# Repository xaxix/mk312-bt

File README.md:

# MK-312BT V1.3

Documentation at : http://tinyurl.com/mk312bt-info

Forum (for questions/discussion): https://metafetish.club ([Estim
Specific Category Here](https://metafetish.club/c/estim), but may not
include all estim messages)

## Board ordering instructions

Preferred board house is https://jlcpcb.com

You'll need 2 gerber zip files from the gerbers directory (click links below to download):

- [MK-312 V1.2 Front Panel](https://github.com/buttshock/mk312-bt/blob/master/gerbers/ZIP%20FILES/MK-312BT%20Front%20Panel%20V1.2%20Gerber.zip?raw=true)
- [MK-312 V1.3 Main Board](https://github.com/buttshock/mk312-bt/blob/master/gerbers/ZIP%20FILES/MK-312BT%20Main%20Boards%20V1.3%20Gerber.zip?raw=true)

**NOTE:** Order Front Panel and Main Board as seperate items (but they
can be in the same cart), due to difference in "Different Design"
setting. See below.

- Base Material: Standard "FR4"
- Layers: "2" Layer (should be detected when you upload the zip with the gerbers)
- Dimensions: (should be detected when you upload the zip with the gerbers)
- Quantity: No requirement, choose whatever you like
- Product Type: "Industrial/Consumer electronics"
- Different Design 
   - Main Boards: "2"
   - Front Panel: "1"
- Delivery Format: "Single PCB"
- Thickness: "1.6"
- PCB Color:
   - Main Boards: No requirement, choose whatever you like
   - Front Panel: Black is recommended, but not required. Choose whatever you like otherwise.
- Silkscreen: "White"
- Surface finish: "LeadFree HASL" or "HASL(with lead)
- Copper weight: 1oz
- Via Covering: Tented (?)
- Board Outline Tolerance: "+-0,2mm(Regular)"
- Confirm Production file: "No"
- Remove Order Number: "No"
- Flying Probe Test: "Fully Test"
- Gold fingers: "No"
- Castellated Holes: "No"
- Edge Plating: "No"
- PCB Remark:
   - Main Boards: V Score the Main Boards panel as indicated.
   - Front Panel: Place all Fab Markings (Serial Numbers/Date Codes) on the BOTTOM side of the front panel board.
   
## Board Assembly Instructions - IMPORTANT

1. Trim Potentiometer knobs to correct length if desired
2. Use black permanent marker to black out front panel hole walls if
   desired
3. Cut the tabs off of the base of the pots so the board sits flush
   with the display facade if desired
4. To correctly fit LCD - solder header to LCD board first. Next
   insert LCD panel into front panel daughter board. Then put screws
   on front panel facade and finger tighten M2.5 screws first. Adjust
   positions as needed so everything lines up and sits well. Finally
   solder LCD header to front panel daughter board.
5. Make sure Pin 32 (LED2) on the HC-05 module is actually soldered
   and making connection to the ZS-040 break out board or "Radio" LED
   may not function on the front panel
6. Be very careful not to bridge pins when soldering the LM 2941
   (U14). Apply heat to 1 pad only and carefully apply solder. If a
   bridge occurs - remove the IC, clean the pads throughly with flux
   and solder wick and then retry. Pins 2 and 3 can be bridged because
   they are both ground. Ensure that no other pins are bridged. Check
   with multimeter continuity tester for bridges before power on!
7. Make sure to check the orientation of all electrolytic caps. (+)
   indicates the positive and a solid white "|" indicates the negative.
8. **MAKE SURE YOUR POWER PLUG IS CENTER POSITIVE OR THINGS WILL GO
   BADLY.** If you fuck up and plug in a reversed polarity supply -
   replace electrolytic caps C1 and C4.
9. Please remember to adjust the LCD contrast potentiometer - if
   incorrectly set the unit and backlight will power on but the
   interface will not be displayed.
10. Place transformers with P facing the output jacks (yes we are
    using the transformers "backwards" if you follow orientation given
    in the transformer datasheet )
11. Trim pins of 4066 IC (U3) Socket on the front panel board flush
    before soldering so buttons can clear. If the buttons still
    interfere, carefully disassemble the button and cut off the bit of
    the plastic housing that interferes with the 4066 IC socket pins.
12. Using side cutters cut off the screw boss/screw mount on the case
    that touches/interferes with the ribbon cable socket on the
    display board.
13. The LCD display has metal retention tabs that may short the
    soldered leads of C43. When installing the display board ensure
    that this does not happen (shorten the capacitor leads and bend
    the offending metal tab out of the way if necessary
14. If Error 20 is encountered on first boot:
   - Check that all FETs and Transformers are turned in the correct direction
   - Check that resistors R35 and R46 are the correct 200k values
   - [See this thread on the message board](https://metafetish.club/t/mk-312bt-failure-20/)

## MK312-BT Firmware

1. We are using an external 8mhz crystal instead of the internal RC
   oscillator that the original uses. We need to set the fuses to
   enable this. 
   - LOW FUSE: 0xFF 
   - HIGH FUSE: 0xDC
2. A patched version of buttshock-et312-frankenbutt-f005 is
   recommended.
3. The firmware needs to be changed to replace the up/down arrows on
   the UI with left right arrows (this is because the LCD we use has a
   different character set)
4. Obtain or modify a copy of the firmware and flash the result onto
   the AVR.
5. If you don't want to use an external crystal - we need to set the
   calibration byte for the internal oscillator. If programming a
   blank chip you first need to read the calibration bytes of that
   part (i.e. using avrdude -t “dump calibration” the fourth byte is
   the calibration byte for 8MHz or use atmel studio to read the
   oscillator calibration byte). Then program that byte into 0x3fff in
   your firmware. These bytes will differ on different chips even from
   the same batch. The firmware reads that byte to set OSCCAL on
   startup. If the byte is inaccurate various problems and failures
   will occur related to timing, interrupts, and serial communication.
   Just use an external crystal dammit.

## MK312-BT Original Fab Notes

(These are the old fab notes from the repo, mostly kept here for
history sake. Ordering instructions above cover most of this.)

### Main Boards

1. V Score the Main Boards panel as indicated.
2. Main Boards has 2 board designs panelized on 1 panel.
3. Thickness is standard 1.6mm (0.063inches)
4. Board is 2 layers
5. HASL Finish - Pb Free Preferred if possible, otherwise Pb HASL is OK
6. 1oz copper
7. FR4 material
8. Main Boards : Green solder mask, White Silkscreen (silkscreen BOTH top and bottom sides)
9. ITAR : NO
10. IPC-A-610 - Class2 (If possible - otherwise ignore)
11. Main Board Dimensions : (193.04mm x 104.14mm) or (7.600 inches x 4.100 inches) 

### Front Panel Boards

1. Place all Fab Markings (Serial Numbers/Date Codes) on the BOTTOM side of the front panel board. 
2. Thickness is standard 1.6mm (0.063inches)
3. Board is 2 layers
4. HASL Finish - Pb Free Preferred if possible, otherwise Pb HASL is OK
5. 1oz copper
6. FR4 material
7. Front Panel Boards : Black Solder Mask, While Silkscreen
8. ITAR : NO
9. IPC-A-610 - Class2 (If possible - otherwise ignore)
10. Front Panel Board Dimensions :  (196.85mm x 58.72mm) or (7.750inches x 2.312inches) 

## Bluetooth Serial Configuration

Refer to
[https://www.itead.cc/wiki/Serial_Port_Bluetooth_Module_(Master/Slave)_:_HC-05](https://www.itead.cc/wiki/Serial_Port_Bluetooth_Module_(Master/Slave)_:_HC-05)
for more information.

```
// Test command to check if we are communicating (expect to receive OK)
AT

//Name the module
AT+NAME=MK-312BT 

//Set baud rate to be same as the ATMEGA16
AT+UART=19200,0,0

//Set the pairing password
AT+PSWD=1234

//Set the LED Indicator polarity (1 = High Drive 0 = Low Drive)
AT+POLAR=1,1

// Reduce power consumption by increasing the scan interval. Without
// this it consumes ~43mA when not connected and causes the 5v regulator
// to get toasty (but still within operational temp range)
AT+IPSCAN=1024,1,1024,1 
```

To do this automatically:
1. Solder Pin32 of the HC05 module (See [bluetooth/HC05PINOUT.PNG](https://github.com/buttshock/mk312-bt/blob/master/bluetooth_conf/HC05PINOUT.png) for reference)
2. Flash the included bin file onto the ATMEGA16
3. Plug the HC-05 bluetooth radio into the board (ensure pin 32 is
   soldered to the carrier board)
4. Place HC-05 in command mode by holding down the button on the HC-05
   module, power up MK-312BT and release button after 2 seconds. LEDs
   on HC-05 will blink slowly (0.5 Hz) to indicate command mode.
5. Watch GUI until it says the HC-05 configuration is finished and
   flash normal firmware back on to the ATMEGA16
6. If program stops on "Communicating with HC-05" make sure OSCCAL
   value for 8 MHz R/C position is copied to &H3FFF of bin location or
   use external 8 MHz crystal with appropriate fuse bits set (FFS use
   the external crystal)

## 3D Printable Case

STL files for a 3D printable case for the MK312 are available in the
case/ directory. For hardware, this case requires:

- 4 M2.5x20 screws
- up to 3 M2.5x5 screws
- some dampening for the battery (double sided foam tape may work)

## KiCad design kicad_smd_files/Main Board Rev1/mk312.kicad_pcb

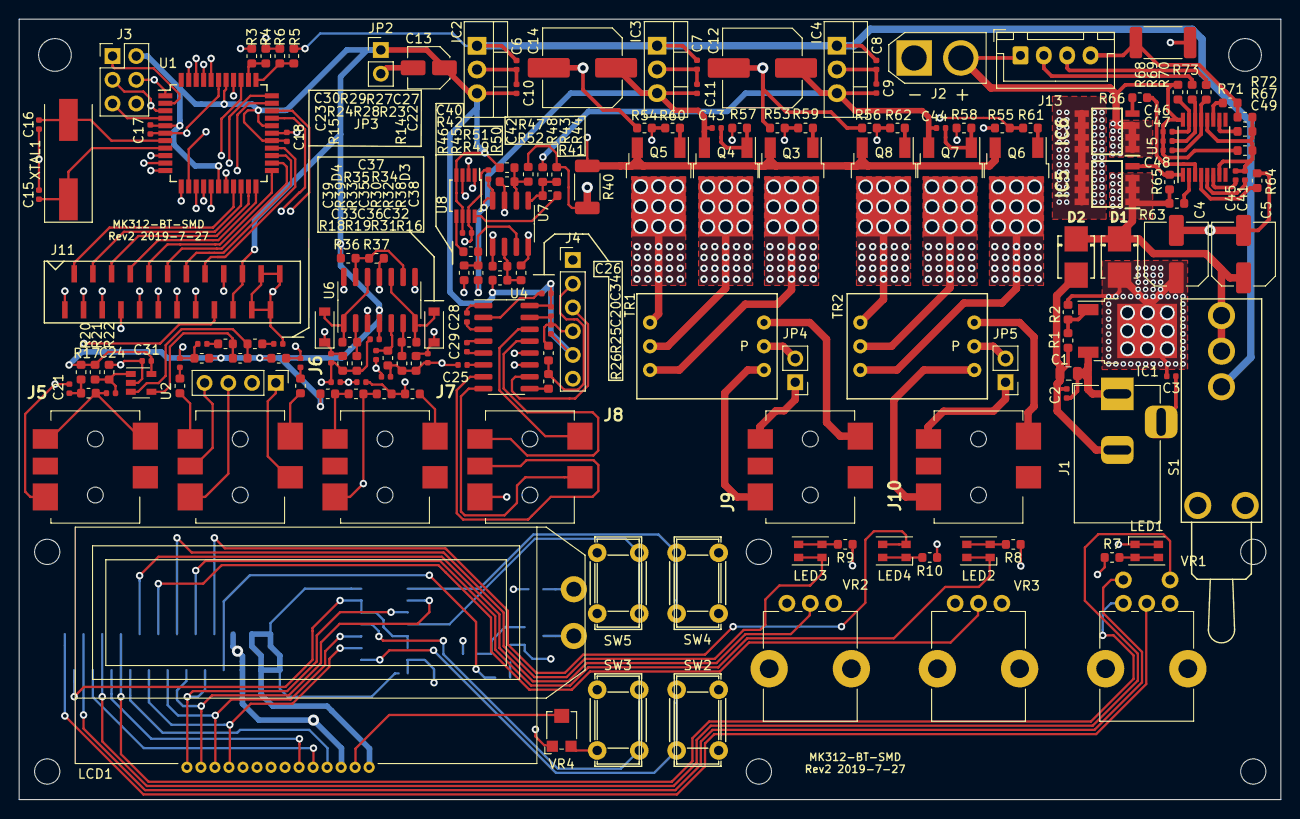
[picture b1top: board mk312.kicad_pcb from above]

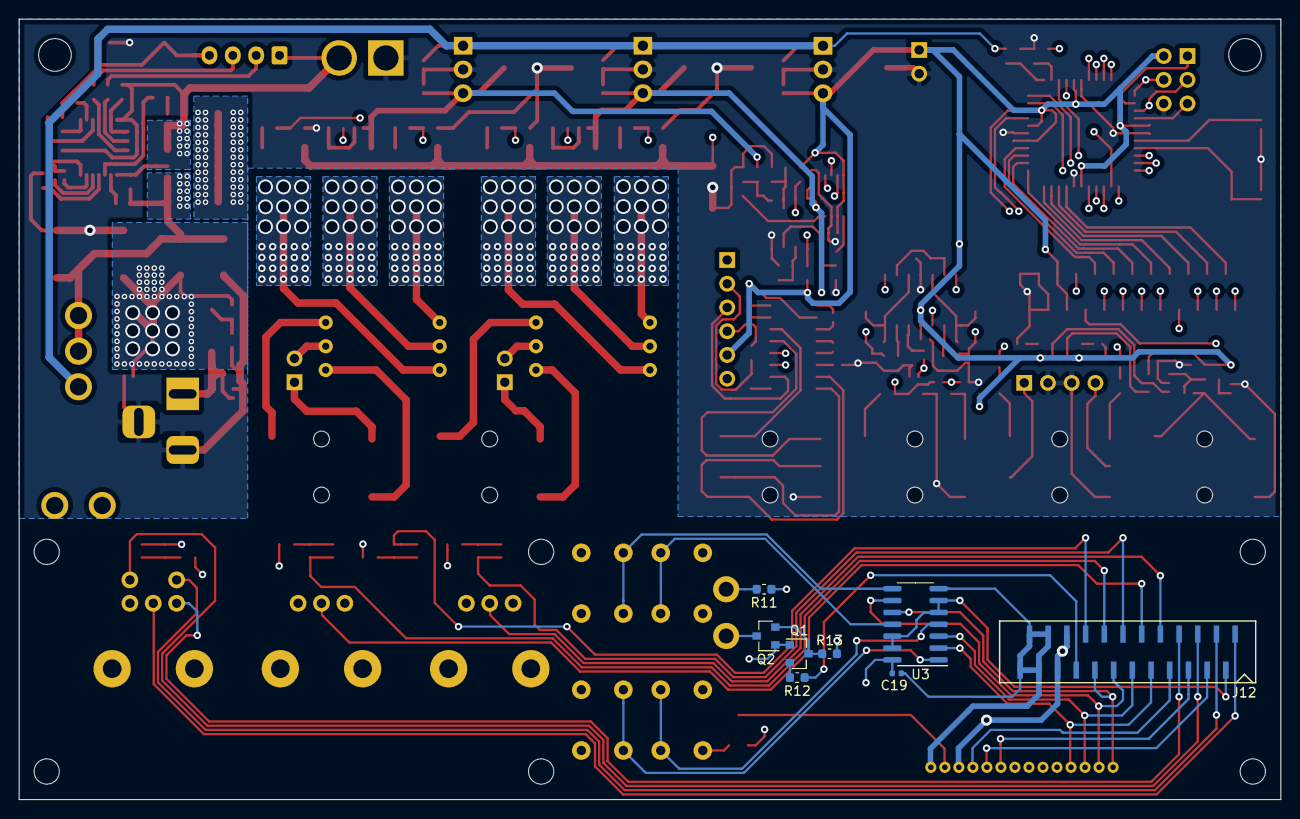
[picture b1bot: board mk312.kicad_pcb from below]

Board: 4 copper layers, 135.0 x 83.5 mm, 190 parts (8 on the bottom side), 161 nets.

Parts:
C1: 10uF; C_0805_2012Metric
C2, C3, C6, C7, C8, C9, C10, C11, C17, C18, C19, C20, C24, C31, C34, C35, C36, C37, C40, C41, C42, C43, C44, C45, C46, C47, C48: 0.1uF; C_0402_1005Metric
C4, C5: 100uF; C_Elec_6.3x7.7
C12, C14: 470uF; C_Elec_8x10.2
C13: 10uF; C_Elec_4x5.8
C15, C16: 18pF; C_0402_1005Metric
C21, C22, C23, C25, C26, C27, C28, C29, C30, C38, C39: 1uF; C_0402_1005Metric
C32, C33: 1nF; C_0402_1005Metric
C49: 2.2uF; C_0603_1608Metric
D1, D2: GF1G-E3/67A; DO-214BA
D3, D4: 1N4148W-E3-08; D_SOD-123
H1, H2, H3, H4, H5, H6: MountingHole; MountingHole_2.7mm_M2.5
H7, H8: MountingHole; MountingHole_3.5mm
IC1: LMS8117ADTX-ADJ; TO-252-2
IC2: L7805CV; TO-220-3_Vertical
IC3, IC4: L7809ABV; TO-220-3_Vertical
IC5, IC6: SI4435FDY-T1-GE3; SOIC127P600X175-8N
J1: Barrel_Jack_MountingPin; BarrelJack_Horizontal
J2: +12V Battery; AMASS_XT30U-M_1x02_P5.0mm_Vertical
J3: Conn_02x03_Odd_Even; PinHeader_2x03_P2.54mm_Vertical
J4: RADIO INTERFACE; PinHeader_1x06_P2.54mm_Vertical
J5: MIC INPUT; SJ13515SMTTR
J6: LINE INPUT; SJ13515SMTTR
J7: REMOTE INPUT; SJ13515SMTTR
J8: LINK INPUT; SJ13515SMTTR
J9: OUTPUT A; SJ13515SMTTR
J10: OUTPUT B; SJ13515SMTTR
J11, J12: Conn_01x24_Male; HFW24S-2STE1LF
J13: Conn_01x04; JST_XH_B4B-XH-A_1x04_P2.50mm_Vertical
JP2: +5V; PinHeader_1x02_P2.54mm_Vertical
JP3: AUX LINE IN; PinHeader_1x04_P2.54mm_Vertical
JP4: A RING; PinHeader_1x02_P2.54mm_Vertical
JP5: B RING; PinHeader_1x02_P2.54mm_Vertical
LCD1: NHD-C0216AZ-FSW-GBW
LED1: POWER; LED_Cree-PLCC4_3.2x2.8mm_CCW
LED2: OUTPUT B; LED_Cree-PLCC4_3.2x2.8mm_CCW
LED3: OUTPUT A; LED_Cree-PLCC4_3.2x2.8mm_CCW
LED4: STATE; LED_Cree-PLCC4_3.2x2.8mm_CCW
Q1, Q2: MMBT3904-7-F; SOT-23
Q3, Q5, Q6, Q8: IRFR9024NTRPBF; TO-252-2
Q4, Q7: IRLR120NTRPBF; TO-252-2
R1, R14, R15, R16, R19, R64, R67, R68, R69, R70, R71: 1K; R_0603_1608Metric
R2: 110; R_0603_1608Metric
R3, R21, R22, R30, R31, R37, R38, R39, R41, R42, R43, R44, R45, R46, R47, R49, R51, R52, R53, R54, R55, R56: 100K; R_0603_1608Metric
R4, R23, R24, R27, R32, R33: 20K; R_0603_1608Metric
R5, R25, R57, R58, R59, R60, R61, R62: 10K; R_0603_1608Metric
R6: 3.3K; R_0603_1608Metric
R7, R8, R9, R10: 390; R_0603_1608Metric
R11: 130; R_0603_1608Metric
R12, R13, R18: 1.5K; R_0603_1608Metric
R17, R20: 2.2K; R_0603_1608Metric
R26, R29: 4.7K; R_0603_1608Metric
R28, R34, R35, R36, R65: 1M; R_0603_1608Metric
R40: 0.5R 1/2W; R_2010_5025Metric
R48, R50: 200K; R_0603_1608Metric
R63, R66: 5.1K; R_0603_1608Metric
R72: 51; R_0603_1608Metric
R73: 0.2R 2W; R_2512_6332Metric
S1: POWER; E-Switch_M7_SPDT
SW2: LEFT/DOWN; E-Switch_Tactile_TL1105
SW3: OK; E-Switch_Tactile_TL1105
SW4: RIGHT/UP; E-Switch_Tactile_TL1105
SW5: MENU; E-Switch_Tactile_TL1105
TR1, TR2: 42TL004; 42TL
U1: ATmega16-16AU; TQFP-44_10x10mm_P0.8mm
U2: MCP6L01U; SOT-23-5
U3: CD4066B; SOIC-14_3.9x8.7mm_P1.27mm
U4: SP232E; SOIC-16_3.9x9.9mm_P1.27mm
U5: S-8254A; TSSOP-16_4.4x5mm_P0.65mm
U6: LM324N; SOIC-14_3.9x8.7mm_P1.27mm
U7: LM358N; SOIC-8_3.9x4.9mm_P1.27mm
U8: LTC1661; MSOP-8_3x3mm_P0.65mm
VR1: MULTI-ADJ; Potentiometer_Alps_RK09K_Dual_Vertical
VR2: LEVEL A; Potentiometer_Alps_RK09K_Single_Vertical
VR3: LEVEL B; Potentiometer_Alps_RK09K_Single_Vertical
VR4: LCD CONTRAST; Potentiometer_Bourns_TC33X_Vertical
XTAL1: 8.0 MHz; Crystal_SMD_HC49-SD

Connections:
+5V: C10.1, C13.1, C17.1, C18.1, C20.1, C26.1, C31.2, C34.2, C37.2, C40.1, IC2.3, J3.2, J4.5, J11.19, J11.20, JP2.1, R18.2, R20.1, R21.1, R23.1, R24.2, R36.2, R47.1, R49.1, U1.5, U1.17, U1.27, U1.29, U1.38, U2.5, U4.16, U6.4, U8.4, U8.6
+5VD: C19.1, J12.19, J12.20, LCD1.3, R7.1, R8.1, R9.1, R11.1, R13.2, U3.14, VR2.3, VR3.3, VR4.1
+9V1: C11.1, C14.1, C42.1, C43.2, IC3.3, Q4.3, R45.1, U7.8
+9V2: C9.1, C12.1, C44.2, IC4.3, Q7.3, R43.1
+12V: C6.1, C7.1, C8.1, IC2.1, IC3.1, IC4.1, R5.2, S1.1
+VDC: C1.1, C2.1, IC1.3, J1.1, R3.1
GND: C1.2, C2.2, C3.2, C4.2, C5.2, C6.2, C7.2, C8.2, C9.2, C10.2, C11.2, C12.2, C13.2, C14.2, C15.2, C16.2, C17.2, C18.2, C20.2, C21.2, C25.1, C27.2, C31.1, C32.2, C33.2, C34.1, C37.1, C38.2, C39.2, C40.2, C42.2, D2.2, IC2.2, IC3.2, IC4.2, J1.2, J1.3, J2.1, J3.6, J4.4, J5.S, J6.S, J7.S, J8.S, J11.21, J11.22, J11.23, J11.24, JP2.2, JP3.2, JP3.3, R1.2, R4.2, R6.2, R19.1, R22.1, R25.2, R30.2, R31.2, R32.2, R33.2, R37.1, R38.1, R39.1, R40.2, R44.2, R46.2, R48.2, R50.2, R53.2, R54.2, R55.2, R56.2, R64.1, R73.2, U1.6, U1.18, U1.28, U1.39, U2.2, U4.15, U6.11, U7.4, U8.7
GNDD: C19.2, J12.21, J12.22, J12.23, J12.24, LCD1.1, LED1.1, Q1.1, Q2.1, R10.1, SW2.2, SW3.2, SW4.2, SW5.2, U3.7, VR1.1, VR2.1, VR3.1, VR4.3
unnamed: C3.1, C4.1, D1.2, IC1.2, R2.2
unnamed: C5.1, D1.1, D2.1, IC5.1, IC5.2, IC5.3, R63.1, R65.1, S1.2, S1.3
unnamed: C15.1, U1.8, XTAL1.1
unnamed: C16.1, U1.7, XTAL1.2
unnamed: C21.1, R17.1, R20.2
unnamed: C22.1, R14.1
unnamed: C23.1, R15.1
unnamed: C24.1, J5.R, J5.T, R17.2
unnamed: C24.2, R21.2, R22.2, U2.1
unnamed: C25.2, U4.6
unnamed: C26.2, U4.2
unnamed: C27.1, R27.2
unnamed: C28.1, U4.1
unnamed: C28.2, U4.3
unnamed: C29.1, U4.4
unnamed: C29.2, U4.5
unnamed: C30.2, R29.2
unnamed: C35.2, R30.1, U6.5
unnamed: C36.2, R16.1, R31.1, U6.3
unnamed: C41.1, U5.5
unnamed: C41.2, C45.2, C49.2, R67.1, R72.2, U5.7, U5.12
unnamed: C43.1, Q4.1, R57.1
unnamed: C44.1, Q7.1, R58.1
unnamed: C45.1, U5.6
unnamed: C46.1, C47.1, C48.1, C49.1, IC6.1, IC6.2, IC6.3, J2.2, J13.1, R68.1, U5.16
unnamed: C46.2, R68.2, U5.15
unnamed: C47.2, R69.2, U5.14
unnamed: C48.2, R70.2, U5.13
unnamed: D3.2, R34.1, U6.7, U6.10
unnamed: D4.2, R35.1, U6.1, U6.12
unnamed: IC1.1, R1.1, R2.1
unnamed: IC5.4, R65.2, U5.1
unnamed: IC5.5, IC5.6, IC5.7, IC5.8, IC6.5, IC6.6, IC6.7, IC6.8
unnamed: IC6.4, R66.1
unnamed: J4.2, R25.1, R26.2
unnamed: J4.3, U4.10
unnamed: J6.R, R15.2
unnamed: J6.RN, JP3.4
unnamed: J6.T, R14.2
unnamed: J6.TN, JP3.1
unnamed: J7.R, R18.1, R19.2
unnamed: J7.T, R16.2
unnamed: J8.R, U4.13
unnamed: J8.RN, U4.7
unnamed: J8.T, U4.14
unnamed: J8.TN, U4.8
unnamed: J9.R, JP4.1
unnamed: J9.S, TR1.1
unnamed: J9.T, TR1.3
unnamed: J10.R, JP5.1
unnamed: J10.S, TR2.1
unnamed: J10.T, TR2.3
unnamed: J13.2, R69.1
unnamed: J13.3, R70.1
unnamed: J13.4, R71.1, R72.1, R73.1
unnamed: JP4.2, TR1.2
unnamed: JP5.2, TR2.2
unnamed: LCD1.2, VR4.2
unnamed: LCD1.A, R11.2
unnamed: LCD1.K, Q2.3
unnamed: LED1.2, R7.2
unnamed: LED2.2, R8.2
unnamed: LED3.2, R9.2
unnamed: LED4.1, R10.2
unnamed: Q1.2, R12.2
unnamed: Q1.3, Q2.2, R13.1
unnamed: Q3.1, R59.1
unnamed: Q3.2, TR1.6
unnamed: Q4.2, TR1.5
unnamed: Q5.1, R60.1
unnamed: Q5.2, TR1.4
unnamed: Q6.1, R61.1
unnamed: Q6.2, TR2.6
unnamed: Q7.2, TR2.5
unnamed: Q8.1, R62.1
unnamed: Q8.2, TR2.4
unnamed: R3.2, R4.1, U1.35
unnamed: R5.1, R6.1, U1.34
unnamed: R26.1, U4.9
unnamed: R27.1, R28.2, U2.3
unnamed: R28.1, R29.1, U2.4
unnamed: R32.1, R34.2, U6.6
unnamed: R33.1, R35.2, U6.2
unnamed: R36.1, R37.2, U6.9, U6.13
unnamed: R41.1, R43.2, R44.1, U7.5
unnamed: R41.2, U8.8
unnamed: R42.1, R45.2, R46.1, U7.3
unnamed: R42.2, U8.5
unnamed: R47.2, R48.1, R52.2, U7.6
unnamed: R49.2, R50.1, R51.2, U7.2
unnamed: R51.1, R57.2, U7.1
unnamed: R52.1, R58.2, U7.7
unnamed: R63.2, U5.2
unnamed: R64.2, U5.4
unnamed: R66.2, U5.3
unnamed: R67.2, U5.10
unnamed: R71.2, U5.11
unnamed: SW2.1, U3.1
unnamed: SW3.1, U3.4
unnamed: SW4.1, U3.8
unnamed: SW5.1, U3.11
PA0: Q3.3, Q5.3, Q6.3, Q8.3, R40.1, U1.37
PA1: C32.1, C35.1, J11.5, U1.36
PA1-PANEL: J12.5, VR1.2
PA4: J11.9, U1.33
PA4-PANEL: J12.9, VR2.2
PA5: J11.11, U1.32
PA5-PANEL: J12.11, VR3.2
PA6: C39.1, D4.1, R39.2, U1.31
PA7: C38.1, D3.1, R38.2, U1.30
PB0: R55.1, R61.2, U1.40
PB1: R56.1, R62.2, U1.41
PB2: R53.1, R59.2, U1.42
PB3: R54.1, R60.2, U1.43
PB5: J3.4, U1.1, U8.3
PB6: J3.1, U1.2
PB7: J3.3, U1.3, U8.2
PC0: J11.2, U1.19
PC0-PANEL: J12.2, U3.5, U3.6, U3.12, U3.13
PC1: J11.4, U1.20
PC1-PANEL: J12.4, LCD1.5
PC2: J11.6, U1.21
PC2-PANEL: J12.6, LCD1.6
PC3: J11.8, U1.22
PC3-PANEL: J12.8, LCD1.4
PC4: J11.10, U1.23
PC4-PANEL: J12.10, LCD1.11, U3.2
PC5: J11.12, U1.24
PC5-PANEL: J12.12, LCD1.12, U3.3
PC6: J11.14, U1.25
PC6-PANEL: J12.14, LCD1.13, U3.9
PC7: J11.16, U1.26
PC7-PANEL: J12.16, LCD1.14, U3.10
PD0: U1.9, U4.12
PD1: U1.10, U4.11
PD2: U1.11, U6.14
PD3: U1.12, U6.8
PD5: J11.15, U1.14
PD5-PANEL: J12.15, LED2.1
PD6: J11.13, U1.15
PD6-PANEL: J12.13, LED3.1
PD7: J11.18, U1.16
PD7-PANEL: J12.18, R12.1
RB4: C33.1, C36.1, J11.7
RB4-PANEL: J12.7, VR1.4
RB9: C23.2, C30.1, J11.3, R24.1
RB9-PANEL: J12.3, VR1.5
RB10: C22.2, J11.1, R23.2
RB10-PANEL: J12.1, VR1.3
STATE: J4.1, J11.17
STATE-PANEL: J12.17, LED4.2
~CS: U1.13, U8.1
~RESET: J3.5, U1.4

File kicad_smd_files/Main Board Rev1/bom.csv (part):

"Item","Qty","Reference(s)","Value","LibPart","Footprint","Datasheet","Allied Price/Stock","Allied_Number","Description","Height","Manufacturer_Name","Manufacturer_Part_Number","Mouser Part Number","Mouser Price/Stock","Notes","RS Part Number","RS Price/Stock"
"1","1","C1","10uF","Device:C_Small","Capacitor_SMD:C_0805_2012Metric","","","","","","Taiyo Yuden","TMK212BBJ106MG-T","963-TMK212BBJ106MG-T","","","",""
"2","27","C2, C3, C6, C7, C8, C9, C10, C11, C17, C18, C19, C20, C24, C31, C34, C35, C36, C37, C40, C41, C42, C43, C44, C45, C46, C47, C48","0.1uF","Device:C_Small","Capacitor_SMD:C_0402_1005Metric","https://www.mouser.com/datasheet/2/281/murata_03122018_GCM_S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","","","","","Murata","GCM155R71C104JA55D","81-GCM155R71C104JA5D","","","",""
"3","2","C4, C5","100uF","Device:CP1","Capacitor_SMD:C_Elec_6.3x7.7","https://www.mouser.com/datasheet/2/315/ABA0000C1240-1130326.pdf","","","","","Panasonic","EEE-HC1C101XP","667-EEE-HC1C101XP","","","",""
"4","2","C12, C14","470uF","Device:CP1","Capacitor_SMD:C_Elec_8x10.2","https://www.mouser.com/datasheet/2/315/ABA0000C1181-947564.pdf","","","","","Panasonic","EEE-FK1C471P","667-EEE-FK1C471P","","","",""
"5","1","C13","10uF","Device:CP1","Capacitor_SMD:C_Elec_4x5.8","https://www.mouser.com/datasheet/2/315/ABA0000C1181-947564.pdf","","","","","Panasonic","EEE-FK1C100R","667-EEE-FK1C100R","","","",""
"6","2","C15, C16","18pF","Device:C_Small","Capacitor_SMD:C_0402_1005Metric","https://www.mouser.com/datasheet/2/281/GCM1555C1H180FA16-01-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","","","","","Murata","GCM1555C1H180FA16J","81-GCM1555C1H180FA6J","","","",""
"7","11","C21, C22, C23, C25, C26, C27, C28, C29, C30, C38, C39","1uF","Device:C_Small","Capacitor_SMD:C_0402_1005Metric","https://www.mouser.com/datasheet/2/281/murata_03052018_GRM_S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","","","","","Murata","GRM155R61C105MA12D","81-GRM155R61C105MA2D","","","",""
"8","2","C32, C33","1nF","Device:C_Small","Capacitor_SMD:C_0402_1005Metric","https://www.mouser.com/datasheet/2/281/murata_03122018_GCM_S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","","","","","Murata","GCM1555C1H102JA16J","81-GCM1555C1H102JA6J","","","",""
"9","1","C49","2.2uF","Device:C_Small","Capacitor_SMD:C_0603_1608Metric","","","","","","KEMET","C0603C225K4PACTU","80-C0603C225K4P","","","",""
"10","2","D1, D2","GF1G-E3/67A","Diode:1N4004","mk312-smd-footprints:DO-214BA","http://www.rectron.com/public/product_datasheets/fm4001w-fm4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","","","Rectifiers 1A, 400V","2.31","Rectron","FM4004W-W","583-FM4004W-W","https://www.mouser.com/Search/Refine.aspx?Keyword=583-FM4004W-W","","",""
"11","2","D3, D4","1N4148W-E3-08","Device:D","Diode_SMD:D_SOD-123","https://www.mouser.com/datasheet/2/427/1n4148w-240387.pdf","","","","","Vishay","1N4148W-E3-08","78-1N4148W-E3-08","","","",""
"12","1","F1","1A Polyfuse","Device:Polyfuse","Fuse:Fuse_2920_7451Metric","https://www.mouser.com/datasheet/2/643/0ZCF_Nov2016-1133542.pdf","","","","","Bel Fuse","0ZCF0100AF2A","530-0ZCF0100AF2A","","","",""
"13","6","H1, H2, H3, H4, H5, H6","MountingHole","Mechanical:MountingHole","MountingHole:MountingHole_2.7mm_M2.5","~","","","","","","","","","","",""
"14","2","H7, H8","MountingHole","Mechanical:MountingHole","MountingHole:MountingHole_3.5mm","~","","","","","","","","","","",""
"15","1","IC1","LMS8117ADTX-ADJ","Regulator_Linear:NCP1117-ADJ_TO252","Package_TO_SOT_SMD:TO-252-2","www.ti.com/lit/ds/symlink/lms8117a.pdf","","","","","Texas Instruments","LMS8117ADTX-ADJ","926-LS8117ADTXADJNPB","","","",""
"16","1","IC2","L7805CV","Regulator_Linear:L7805","Package_TO_SOT_THT:TO-220-3_Vertical","https://www.mouser.com/datasheet/2/389/l78-974043.pdf","http://www.alliedelec.com/stmicroelectronics-l7805abd2t-tr/7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","70407657","","4.6","STMicroelectronics","L7805CV","511-L7805CV","https://www.mouser.com/Search/Refine.aspx?Keyword=511-L7805ABD2T-TR","","7931342P","http://uk.rs-online.com/web/p/products/7931342P"
"17","2","IC3, IC4","L7809ABV","Regulator_Linear:L7809","Package_TO_SOT_THT:TO-220-3_Vertical","https://www.mouser.com/datasheet/2/389/l78-974043.pdf","","","","","STMicroelectronics","L7809ABV","511-L7809ABV","https://www.mouser.com/Search/Refine.aspx?Keyword=511-L7809ABD2T-TR","","",""
"18","2","IC5, IC6","SI4435FDY-T1-GE3","SamacSys_Parts:SI4435FDY-T1-GE3","mk312-smd-footprints:SOIC127P600X175-8N","http://www.vishay.com/docs/75339/si4435fdy.pdf","","","MOSFET -30V Vds 20V Vgs SO-8","1.75","Vishay","SI4435FDY-T1-GE3","78-SI4435FDY-T1-GE3","https://www.mouser.com/Search/Refine.aspx?Keyword=78-SI4435F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","","",""
"19","1","J1","Barrel_Jack_MountingPin","Connector:Barrel_Jack_Switch","Connector_BarrelJack:BarrelJack_Horizontal","https://www.mouser.com/datasheet/2/670/pj-002a-1312176.pdf","","","","","CUI","PJ-002A","490-PJ-002A","","","",""
"20","1","J2","+12V Battery","Connector_Generic:Conn_01x02","Connector_AMASS:AMASS_XT30U-M_1x02_P5.0mm_Vertical","~","","","","","","","","","","",""
"21","1","J3","Conn_02x03_Odd_Even","Connector_Generic:Conn_02x03_Odd_Even","Connector_PinHeader_2.54mm:PinHeader_2x03_P2.54mm_Vertical","https://www.mouser.com/datasheet/2/418/NG_CD_103328_P5-1229876.pdf","","","","","TE Connectivity / AMP","4-103328-2","571-4-103328-2","","","",""
"22","1","J4","RADIO INTERFACE","Connector_Generic:Conn_01x06","Connector_PinHeader_2.54mm:PinHeader_1x06_P2.54mm_Vertical","https://www.mouser.com/datasheet/2/527/slw-1370256.pdf","","","","","Samtec","SLW-106-01-G-S","200-SLW10601GS","","","",""
"23","1","J5","MIC INPUT","Connector:AudioJack3_SwitchTR","mk312-smd-footprints:SJ13515SMTTR","https://www.mouser.com/datasheet/2/670/sj1-351x-smt_series-1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","","","","","CUI","SJ1-3515-SMT-TR","490-SJ1-3515-SMT-TR","","","",""
"24","1","J6","LINE INPUT","Connector:AudioJack3_SwitchTR","mk312-smd-footprints:SJ13515SMTTR","https://www.mouser.com/datasheet/2/670/sj1-351x-smt_series-1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","","","","","CUI","SJ1-3515-SMT-TR","490-SJ1-3515-SMT-TR","","","",""
"25","1","J7","REMOTE INPUT","Connector:AudioJack3_SwitchTR","mk312-smd-footprints:SJ13515SMTTR","https://www.mouser.com/datasheet/2/670/sj1-351x-smt_series-1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","","","","","CUI","SJ1-3515-SMT-TR","490-SJ1-3515-SMT-TR","","","",""
"26","1","J8","LINK INPUT","Connector:AudioJack3_SwitchTR","mk312-smd-footprints:SJ13515SMTTR","https://www.mouser.com/datasheet/2/670/sj1-351x-smt_series-1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","","","","","CUI","SJ1-3515-SMT-TR","490-SJ1-3515-SMT-TR","","","",""
"27","1","J9","OUTPUT A","Connector:AudioJack3_SwitchTR","mk312-smd-footprints:SJ13515SMTTR","https://www.mouser.com/datasheet/2/670/sj1-351x-smt_series-1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","","","","","CUI","SJ1-3515-SMT-TR","490-SJ1-3515-SMT-TR","","","",""
"28","1","J10","OUTPUT B","Connector:AudioJack3_SwitchTR","mk312-smd-footprints:SJ13515SMTTR","https://www.mouser.com/datasheet/2/670/sj1-351x-smt_series-1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","","","","","CUI","SJ1-3515-SMT-TR","490-SJ1-3515-SMT-TR","","","",""
"29","1","J11","Conn_01x24_Male","Connector:Conn_01x24_Male","mk312-smd-footprints:HFW24S-2STE1LF","https://www.mouser.com/datasheet/2/18/hfw_s-2ste1lf-1365432.pdf","","","","","Amphenol FCI","HFW24S-2STE1LF","649-HFW24S-2STE1LF","","","",""
"30","1","J12","Conn_01x24_Male","mk312:Conn_01x24_Male_Power","mk312-smd-footprints:HFW24S-2STE1LF","https://www.mouser.com/datasheet/2/18/hfw_s-2ste1lf-1365432.pdf","","","","","Amphenol FCI","HFW24S-2STE1LF","649-HFW24S-2STE1LF","","","",""
"31","1","J13","Conn_01x04","Connector_Generic:Conn_01x04","Connector_JST:JST_XH_B4B-XH-A_1x04_P2.50mm_Vertical","~","","","","","","","","","","",""
"32","1","JP2","+5V","Connector_Generic:Conn_01x02","Connector_PinHeader_2.54mm:PinHeader_1x02_P2.54mm_Vertical","https://www.mouser.com/datasheet/2/418/NG_CD_146285_J-649398.pdf","","","","","TE Connectivity","5-146285-2","571-5-146285-2","","","",""
"33","1","JP3","AUX LINE IN","Connector_Generic:Conn_01x04","Connector_PinHeader_2.54mm:PinHeader_1x04_P2.54mm_Vertical","https://www.mouser.com/datasheet/2/418/NG_CD_146285_J-649398.pdf","","","","","TE Connectivity","5-146285-2","571-5-146285-2","","","",""
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
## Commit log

2018-11-11 Add v1.3 gerbers
2018-11-11 Update README with ordering info
2018-11-11 Move assembly instructions into README
2018-11-11 Instruction updates
2018-11-11 Change firmware README to markdown
2018-11-11 Add fab notes to readme, update instructions
2018-11-11 Add bluetooth config to README
2018-11-12 Remove v1.3 gerbers missing V-Cuts
2018-11-12 Fix Gerber 1.3 output using Seeed exporter in Eagle 9
2018-11-20 Update repo with V1.3 gerbers with value layers
2018-12-19 3d printable case.
    requires 4 M2.5x20, up to 3 M2.5x5, and some dampening for the battery.
2018-12-19 Add 3D Printed case hardware instructions to README
2019-05-22 Kicad SMD version of mk312bt
2019-05-25 Case design, Kicad updates, part substitutions, etc
2019-05-25 Added case design for smd version
2019-05-25 Updated BOM, exported previews of PCB and schematic
2019-08-05 Firmware patch to support new LCD, more beefy power circuit for LiPo, added LiPo Balance and protection, fixed reversed op-amp comparitor pins
